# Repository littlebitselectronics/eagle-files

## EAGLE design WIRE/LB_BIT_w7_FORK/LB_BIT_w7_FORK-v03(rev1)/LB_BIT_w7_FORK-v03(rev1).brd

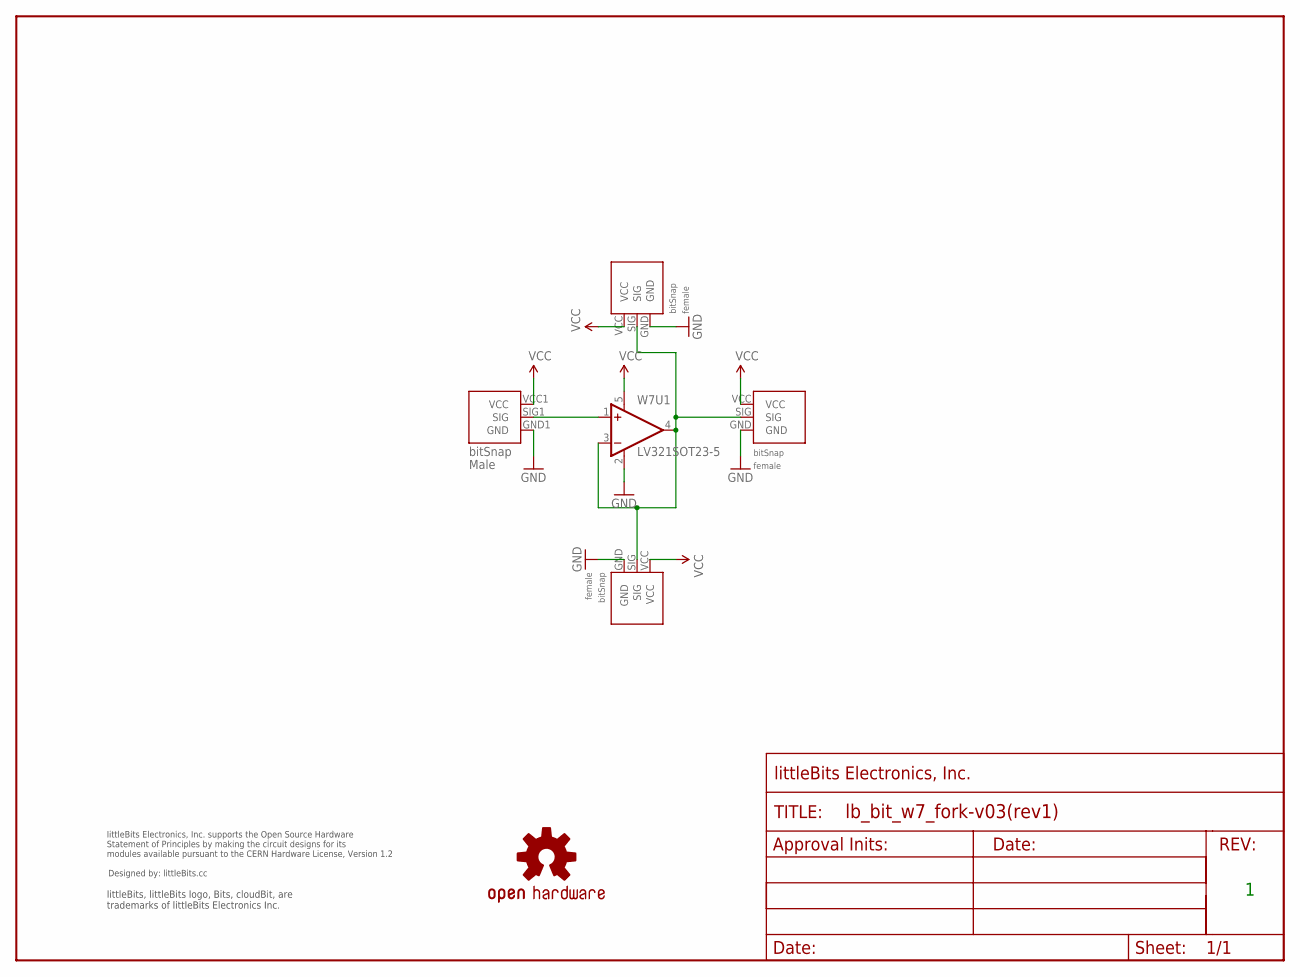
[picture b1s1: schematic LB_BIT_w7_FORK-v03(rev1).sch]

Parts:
FRAME1: FRAME-LETTER-OHWOHW; FABDWG01-OHW
U$2: OSHW-LOGOL; OSHW-LOGO-L
U$12: OSHWCREDIT
W7BSF1, W7BSF2, W7BSF3: BITSNAP_V03_FEMALE
W7BSM1: BITSNAP_V03_MALE
W7U1: LV321SOT23-5; SOT23-5

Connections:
GND: W7BSF1.GND, W7BSF2.GND, W7BSF3.GND, W7BSM1.GND1 (GND), W7U1.2 (V-)
unnamed: W7BSM1.SIG1 (SIG), W7U1.1 (+IN)
unnamed: W7BSF1.SIG, W7BSF2.SIG, W7BSF3.SIG, W7U1.3 (-IN), W7U1.4 (OUT)
VCC: W7BSF1.VCC, W7BSF2.VCC, W7BSF3.VCC, W7BSM1.VCC1 (VCC), W7U1.5 (V+)

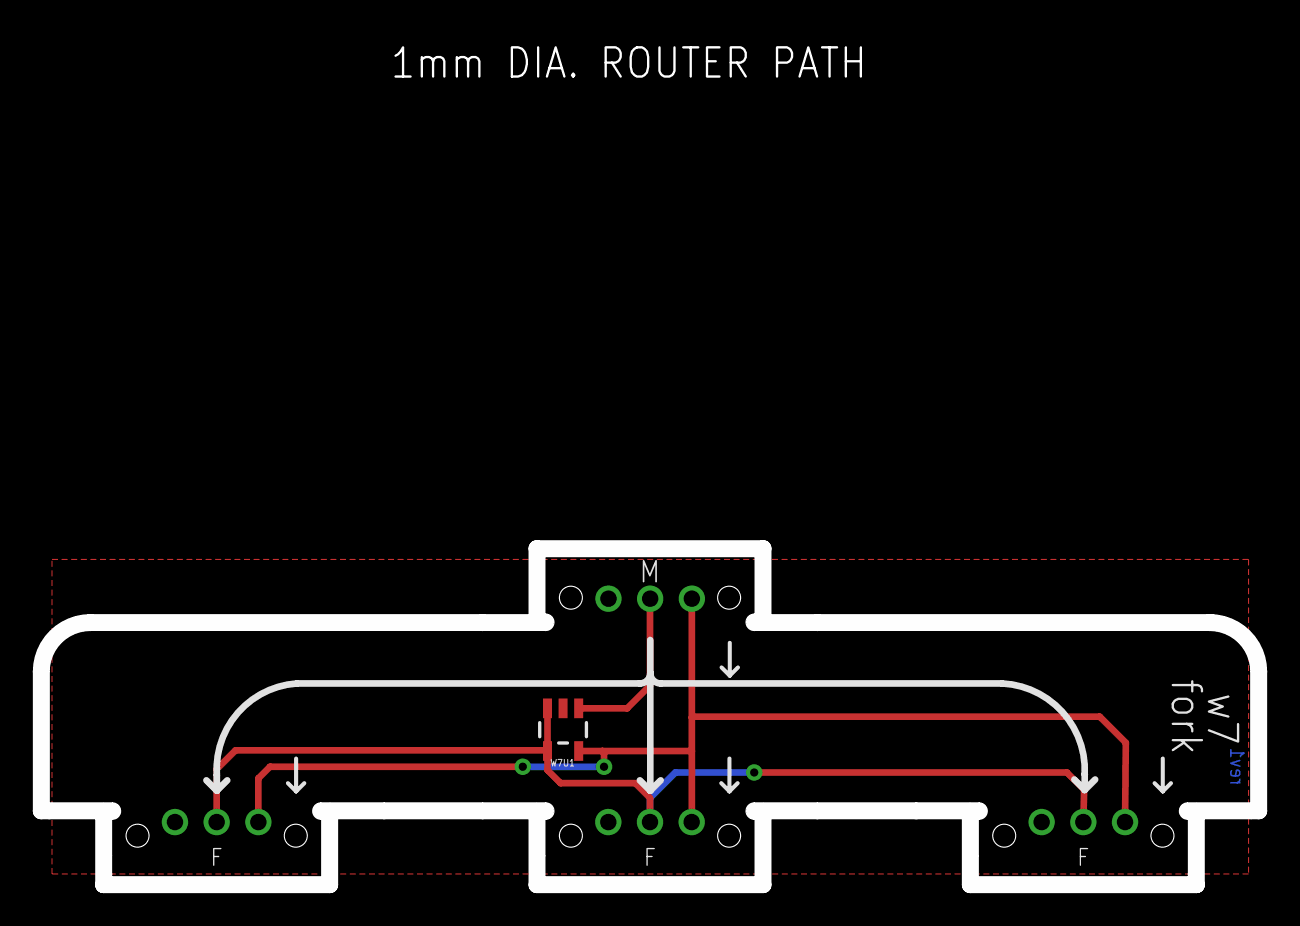
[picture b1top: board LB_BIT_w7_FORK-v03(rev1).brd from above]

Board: 2 copper layers, 74.2 x 20.5 mm, 9 parts (0 on the bottom side), 4 nets.

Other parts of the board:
U$8: OSHW_FILLX150_NOTEXT

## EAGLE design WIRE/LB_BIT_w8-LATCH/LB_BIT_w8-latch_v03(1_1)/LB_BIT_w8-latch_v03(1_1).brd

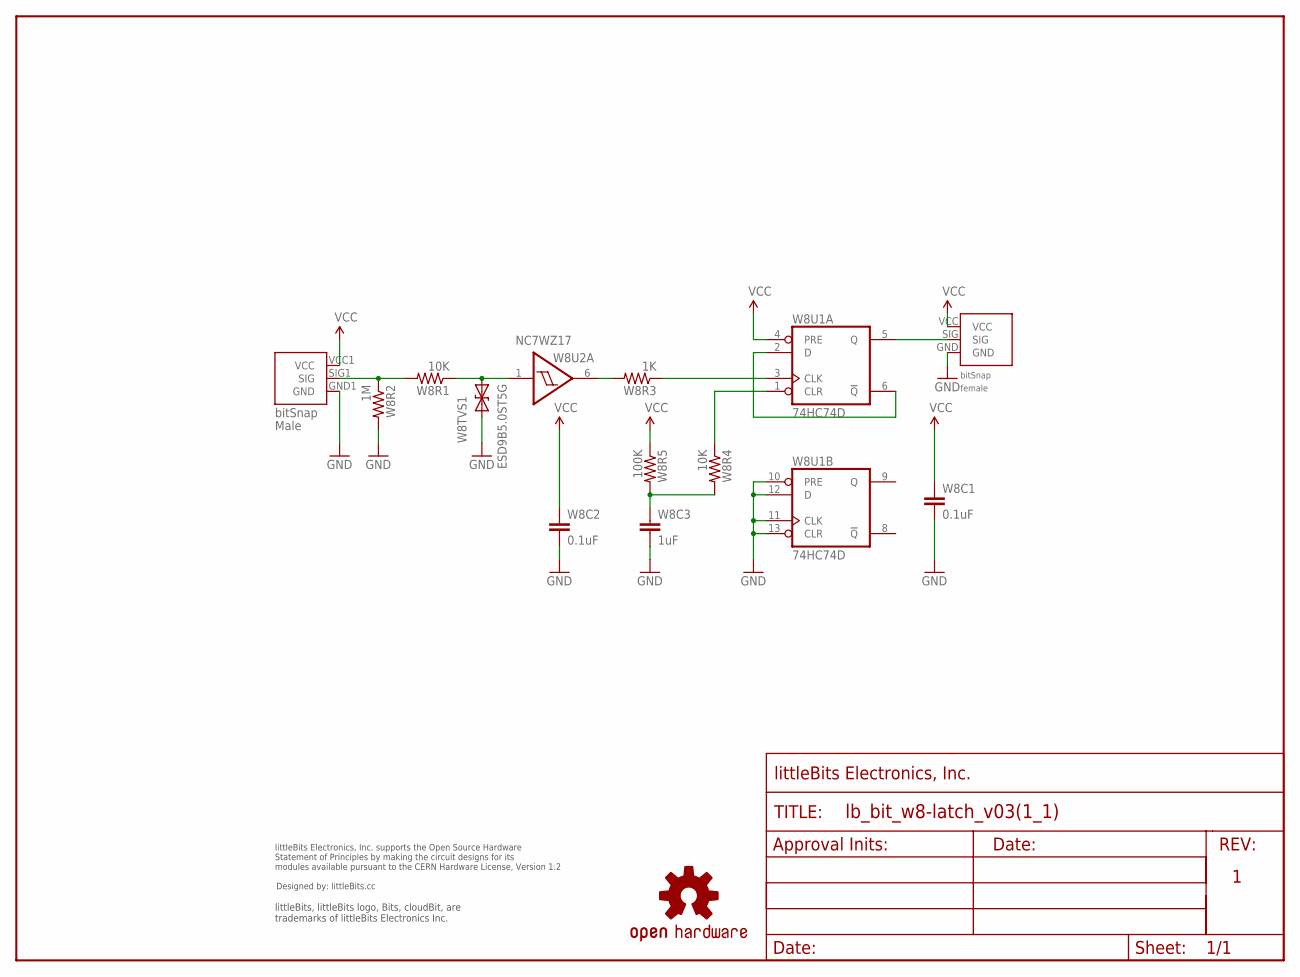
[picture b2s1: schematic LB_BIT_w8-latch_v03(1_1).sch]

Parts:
U$1: OSHW-LOGOL; OSHW-LOGO-L
U$2: OSHWCREDIT
U$12: FRAME-LETTER-OHWOHW; FABDWG01-OHW
W8BSF1: BITSNAP_V03_FEMALE
W8BSM1: BITSNAP_V03_MALE
W8C1, W8C2: 0.1uF; 0603-CAP
W8C3: 1uF; 0603-CAP
W8R1, W8R4: 10K; 0603-RES
W8R2: 1M; 0603-RES
W8R3: 1K; 0603-RES
W8R5: 100K; 0603-RES
W8TVS1: ESD9B5.0ST5G; SOD-923
W8U1: 74HC74D; SO14
W8U2: SCHMITT_TRIGGER_NON_INVERTINGNC7WZ17; SC70-6

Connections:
D1: W8U1.2 (D), W8U1.6 (!Q)
GND: W8BSF1.GND, W8BSM1.GND1 (GND), W8C1.2, W8C2.2, W8C3.2, W8R2.2, W8TVS1.1 (A), W8U1.7 (GND), W8U1.10 (PRE), W8U1.11 (CLK), W8U1.12 (D), W8U1.13 (CLR), W8U2.2 (GND)
unnamed: W8R3.2, W8U2.6 (O)
unnamed: W8BSM1.SIG1 (SIG), W8R1.2, W8R2.1
unnamed: W8R1.1, W8TVS1.2 (C), W8U2.1 (I)
unnamed: W8BSF1.SIG, W8U1.5 (Q)
unnamed: W8R4.1, W8U1.1 (CLR)
unnamed: W8C3.1, W8R4.2, W8R5.2
unnamed: W8R3.1, W8U1.3 (CLK)
VCC: W8BSF1.VCC, W8BSM1.VCC1 (VCC), W8C1.1, W8C2.1, W8R5.1, W8U1.4 (PRE), W8U1.14 (VCC), W8U2.5 (VCC)

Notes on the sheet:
NC7WZ17

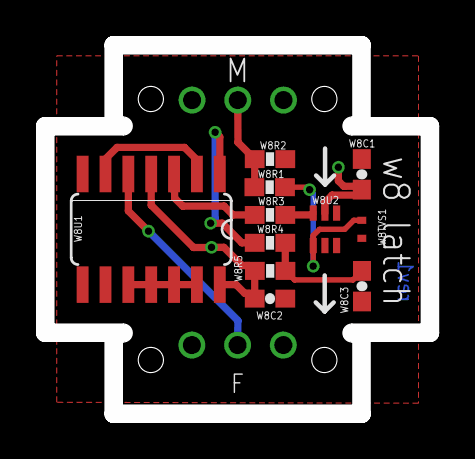
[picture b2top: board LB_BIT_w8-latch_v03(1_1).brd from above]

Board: 2 copper layers, 21.4 x 20.5 mm, 17 parts (0 on the bottom side), 10 nets.

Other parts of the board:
U$10: OSHW_FILLX150_NOTEXT

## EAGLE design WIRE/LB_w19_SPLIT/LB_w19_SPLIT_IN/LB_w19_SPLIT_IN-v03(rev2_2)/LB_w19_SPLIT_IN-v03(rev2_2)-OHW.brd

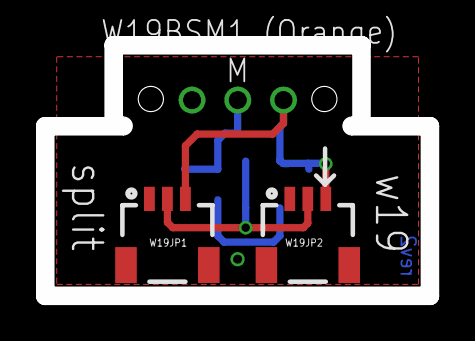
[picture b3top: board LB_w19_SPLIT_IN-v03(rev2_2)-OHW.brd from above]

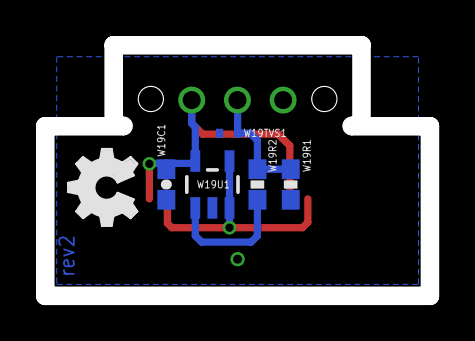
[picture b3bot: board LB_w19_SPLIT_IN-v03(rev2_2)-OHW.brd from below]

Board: 2 copper layers, 21.4 x 13.9 mm, 12 parts (5 on the bottom side), 5 nets.

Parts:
E$1: FABDWG01-OHW
E$2: OSHWCREDIT-KORG
U$2: OSHW_FILLX150_NOTEXT
U$3: OSHW-LOGOL; OSHW-LOGO-L
W19BSM1: BITSNAP_V03_MALE
W19C1: 0.1uf; CAP-0603
W19JP1, W19JP2: 1X03-1MM-RA
W19R1: 1M; RES-0603
W19R2: 10K; RES-0603
W19TVS1: ESD9B5.0ST5G; SOD-923
W19U1: LV321SOT23-5; SOT23-5

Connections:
GND: W19BSM1.GND1, W19C1.2, W19JP1.1, W19JP2.1, W19R1.1, W19TVS1.1, W19U1.2
unnamed: W19BSM1.SIG1, W19R1.2, W19R2.2, W19TVS1.2
unnamed: W19R2.1, W19U1.1
unnamed: W19JP1.2, W19JP2.2, W19U1.3, W19U1.4
VCC: W19BSM1.VCC1, W19C1.1, W19JP1.3, W19JP2.3, W19U1.5

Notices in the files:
parts and their libraries:
LITTLEBITS: modules available pursuant to the CERN Hardware License,
Version 1.2
LITTLEBITS: modules available pursuant to the CERN Hardware License, Version 1.2
SparkFun: Licensing: CC v3.0 Share-Alike You are welcome to use this library for commercial purposes.
